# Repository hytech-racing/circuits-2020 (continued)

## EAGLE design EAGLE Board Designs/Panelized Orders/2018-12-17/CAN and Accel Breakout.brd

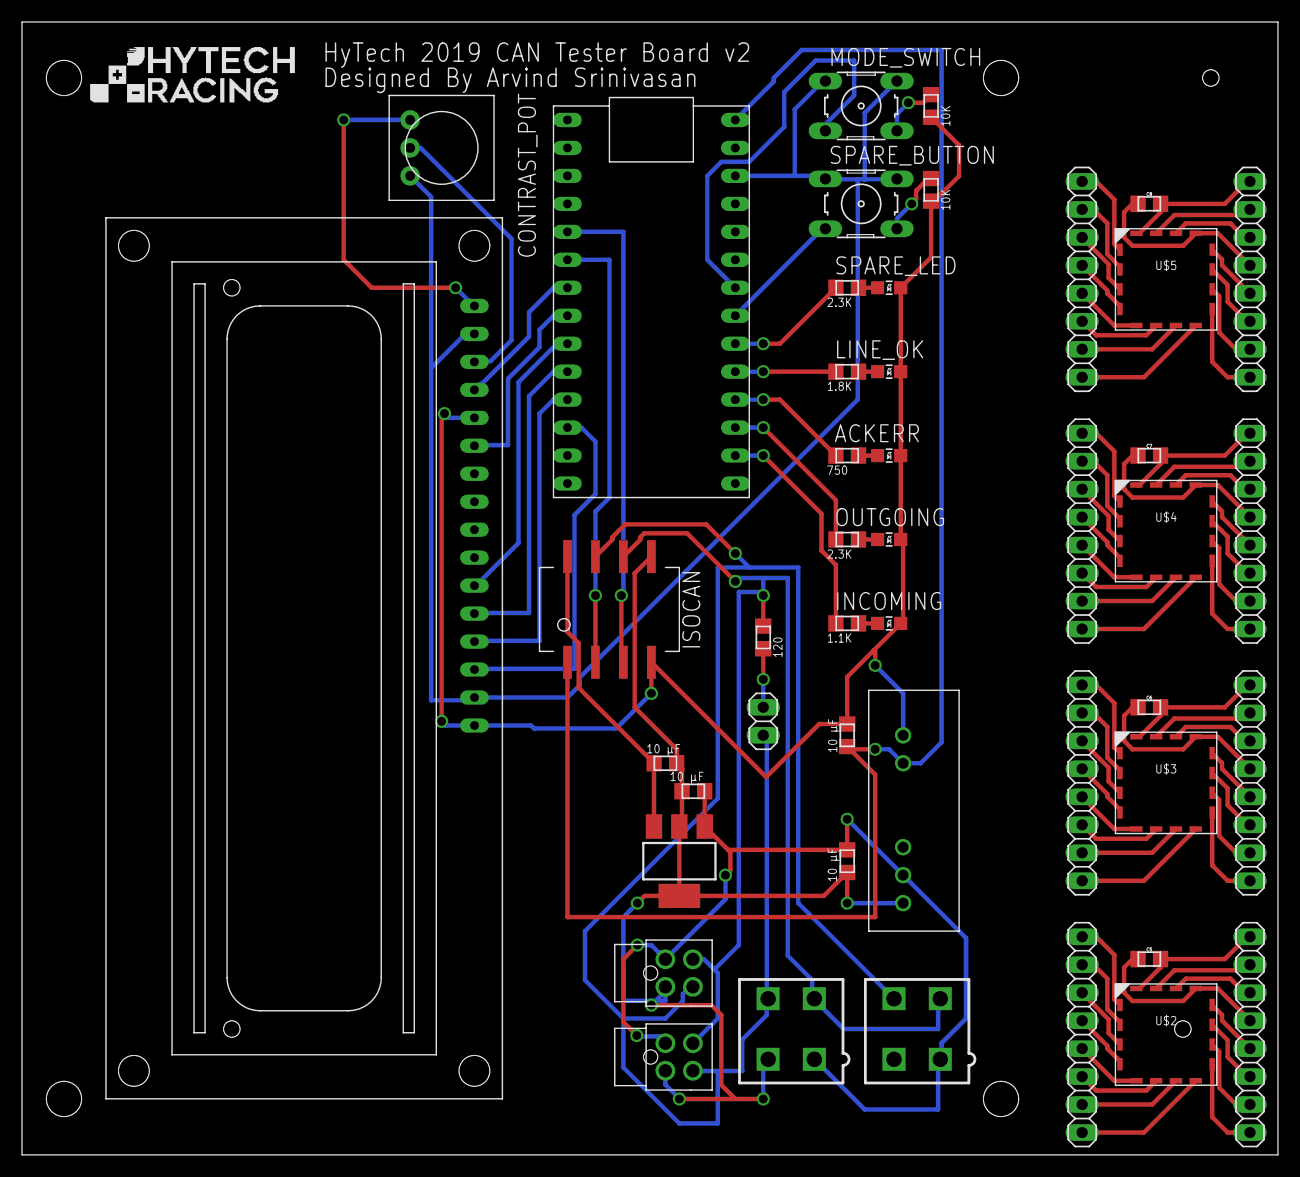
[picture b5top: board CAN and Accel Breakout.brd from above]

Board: 2 copper layers, 114.0 x 102.9 mm, 46 parts (0 on the bottom side), 96 nets.

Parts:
5V_REGULATOR: SOT223
ACKERR: ORANGE; LED-805
C1, C2, C3, C4: 10 μF; 0805
C5, C6, C7, C8: 1µF; 0805
CAN_TERMINATION_RESISTOR: 120; 0805
CONTRAST_POT: 10k; TRIM-3386
INCOMING: YELLOW; LED-805
JP1: M02; 1X02
JP2, JP3, JP4, JP5, JP6, JP7, JP8, JP9: 1X08
LINE_OK: GREEN; LED-805
M1: Minifit-1; MINIFIT_5566-4
M2: Minifit-2; MINIFIT_5566-4
M3: Nanofit-1; NANO-FIT_VERTICAL-4
M4: Nanofit-2; NANO-FIT_VERTICAL-4
MODE_SWITCH: B3F-10XX
OUTGOING: BLUE; LED-805
R1: 1.1K; 0805
R2, R5: 2.3K; 0805
R3: 750; 0805
R4: 1.8K; 0805
R_MODE_SWITCH: 10K; 0805
R_SPARE_BUTTON: 10K; 0805
SPARE_BUTTON: B3F-10XX
SPARE_LED: WHITE; LED-805
U1: ISOCAN; DUB8
U3: TEENSY_3.2_SIMPLE
U4: CHARACTER_LCD; LCD1602
U$1: NCS1S1205SC-12V-5VCONVERTER; DCDC-CONVERTER
U$2, U$3, U$4, U$5: ADIS16209; CC-16-2

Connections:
+3V3_ISOLATED: CONTRAST_POT.3, MODE_SWITCH.1, MODE_SWITCH.2, SPARE_BUTTON.1, SPARE_BUTTON.2, U3.3.3V, U4.2, U4.15
+5V: 5V_REGULATOR.3, C2.1, U1.P$8
+5V_ISOLATED: C3.1, U1.P$1, U3.VIN, U$1.+VOUT
+12V: 5V_REGULATOR.1, C1.1, C4.1, M1.1, M2.1, M3.P$1, M4.P$1, U$1.+VIN
CANH: JP1.1, M1.4, M2.4, M3.P$4, M4.P$4, U1.P$7
CANL: CAN_TERMINATION_RESISTOR.1, M1.3, M2.3, M3.P$3, M4.P$3, U1.P$6
CANRX: U1.P$2, U3.D4(CANRX)
CANTX: U1.P$3, U3.D3(CANTX)
GND: 5V_REGULATOR.2, 5V_REGULATOR.4, C1.2, C2.2, C4.2, M1.2, M2.2, M3.P$2, M4.P$2, U1.P$5, U$1.-VIN
GND1: C5.2, JP3.1, U$2.P$16
GND2: C6.2, JP5.1, U$3.P$16
GND3: C7.2, JP7.1, U$4.P$16
GND4: C8.2, JP9.1, U$5.P$16
GND_ISOLATED: ACKERR.C, C3.2, CONTRAST_POT.1, INCOMING.C, LINE_OK.C, OUTGOING.C, R_MODE_SWITCH.2, R_SPARE_BUTTON.2, SPARE_LED.C, U1.P$4, U3.GND, U4.1, U4.5, U4.16, U$1.-VOUT
unnamed: R1.2, U3.A0
unnamed: R5.1, SPARE_LED.A
unnamed: SPARE_BUTTON.3, U3.A5
unnamed: R2.2, U3.A1
unnamed: R3.2, U3.A2
unnamed: R4.2, U3.A3
unnamed: R5.2, U3.A4
unnamed: LINE_OK.A, R4.1
unnamed: ACKERR.A, R3.1
unnamed: OUTGOING.A, R2.1
unnamed: INCOMING.A, R1.1
unnamed: MODE_SWITCH.4, R_MODE_SWITCH.1
unnamed: MODE_SWITCH.3, U3.A6
unnamed: R_SPARE_BUTTON.1, SPARE_BUTTON.4
unnamed: CAN_TERMINATION_RESISTOR.2, JP1.2
unnamed: JP2.1, U$2.P$1
unnamed: U3.D5, U4.4
unnamed: U3.D6, U4.6
unnamed: U3.D7(RX3), U4.11
unnamed: U3.D8(TX3), U4.12
unnamed: U3.D9(RX2), U4.13
unnamed: U3.D10(TX2), U4.14
unnamed: JP2.2, U$2.P$2
unnamed: JP2.3, U$2.P$3
unnamed: JP2.4, U$2.P$4
unnamed: JP2.5, U$2.P$5
unnamed: JP2.6, U$2.P$6
unnamed: JP2.7, U$2.P$7
unnamed: JP2.8, U$2.P$8
unnamed: JP3.2, U$2.P$15
unnamed: JP3.3, U$2.P$14
unnamed: C5.1, JP3.4, U$2.P$13
unnamed: JP3.5, U$2.P$12
unnamed: JP3.6, U$2.P$11
unnamed: JP3.7, U$2.P$10
unnamed: JP3.8, U$2.P$9
unnamed: JP4.1, U$3.P$1
unnamed: JP4.2, U$3.P$2
unnamed: JP4.3, U$3.P$3
unnamed: JP4.4, U$3.P$4
unnamed: JP4.5, U$3.P$5
unnamed: JP4.6, U$3.P$6
unnamed: JP4.7, U$3.P$7
unnamed: JP4.8, U$3.P$8
unnamed: JP5.2, U$3.P$15
unnamed: JP5.3, U$3.P$14
unnamed: C6.1, JP5.4, U$3.P$13
unnamed: JP5.5, U$3.P$12
unnamed: JP5.6, U$3.P$11
unnamed: JP5.7, U$3.P$10
unnamed: JP5.8, U$3.P$9
unnamed: JP6.1, U$4.P$1
unnamed: JP6.2, U$4.P$2
unnamed: JP6.3, U$4.P$3
unnamed: JP6.4, U$4.P$4
unnamed: JP6.5, U$4.P$5
unnamed: JP6.6, U$4.P$6
unnamed: JP6.7, U$4.P$7
unnamed: JP6.8, U$4.P$8
unnamed: JP7.2, U$4.P$15
unnamed: JP7.3, U$4.P$14
unnamed: C7.1, JP7.4, U$4.P$13
unnamed: JP7.5, U$4.P$12
unnamed: JP7.6, U$4.P$11
unnamed: JP7.7, U$4.P$10
unnamed: JP7.8, U$4.P$9
unnamed: JP8.1, U$5.P$1
unnamed: JP8.2, U$5.P$2
unnamed: JP8.3, U$5.P$3
unnamed: JP8.4, U$5.P$4
unnamed: JP8.5, U$5.P$5
unnamed: JP8.6, U$5.P$6
unnamed: JP8.7, U$5.P$7
unnamed: JP8.8, U$5.P$8
unnamed: JP9.2, U$5.P$15
unnamed: JP9.3, U$5.P$14
unnamed: C8.1, JP9.4, U$5.P$13
unnamed: JP9.5, U$5.P$12
unnamed: JP9.6, U$5.P$11
unnamed: JP9.7, U$5.P$10
unnamed: JP9.8, U$5.P$9
VO: CONTRAST_POT.2, U4.3

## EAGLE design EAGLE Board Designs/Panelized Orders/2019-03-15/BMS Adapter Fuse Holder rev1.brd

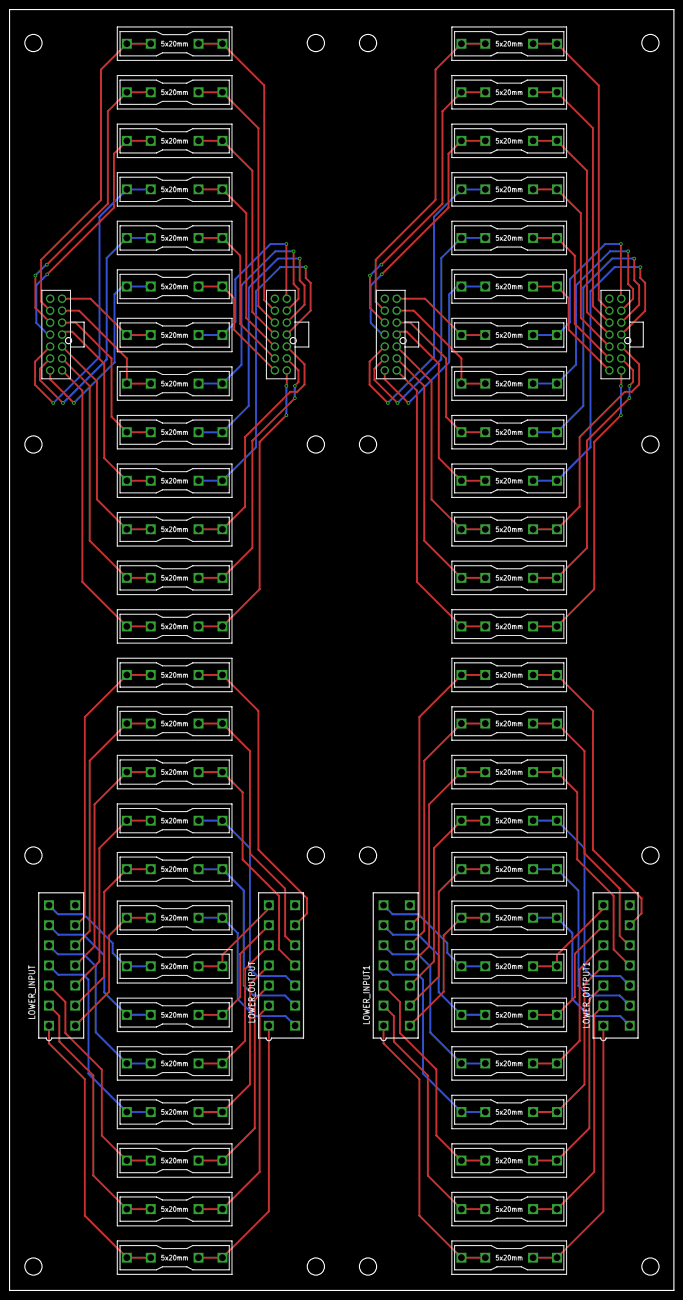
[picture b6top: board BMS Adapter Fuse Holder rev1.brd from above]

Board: 2 copper layers, 139.0 x 268.0 mm, 60 parts (0 on the bottom side), 104 nets.

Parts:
LOWER_INPUT, LOWER_INPUT1: CONNECTOR-14; MINIFIT_5566-14
LOWER_OUTPUT, LOWER_OUTPUT1: CONNECTOR-14; MINIFIT_5566-14
U$1, U$2, U$3, U$4, U$5, U$6, U$7, U$8, U$9, U$10, U$11, U$12, U$13, U$14, U$15, U$16, U$17, U$18, U$19, U$20, U$21, U$22, U$23, U$24, U$25, U$26, U$27, U$28, U$29, U$30, U$31, U$32, U$33, U$34, U$35, U$36, U$37, U$38, U$39, U$40, U$41, U$42, U$43, U$44, U$45, U$46, U$47, U$48, U$49, U$50, U$51, U$52: 1A; 0751.0110
UPPER_INPUT, UPPER_INPUT1: CONNECTOR-14NANO-FIT_VERTICAL-14; NANO-FIT_VERTICAL-14
UPPER_OUTPUT, UPPER_OUTPUT1: CONNECTOR-14NANO-FIT_VERTICAL-14; NANO-FIT_VERTICAL-14

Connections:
unnamed: LOWER_OUTPUT.1, U$1.L1, U$1.L2
unnamed: LOWER_OUTPUT.2, U$2.L1, U$2.L2
unnamed: LOWER_OUTPUT.3, U$3.L1, U$3.L2
unnamed: LOWER_OUTPUT.4, U$4.L1, U$4.L2
unnamed: LOWER_OUTPUT.5, U$5.L1, U$5.L2
unnamed: LOWER_OUTPUT.6, U$6.L1, U$6.L2
unnamed: LOWER_OUTPUT.7, U$7.L1, U$7.L2
unnamed: LOWER_OUTPUT.8, U$8.L1, U$8.L2
unnamed: LOWER_OUTPUT.9, U$9.L1, U$9.L2
unnamed: LOWER_OUTPUT.10, U$10.L1, U$10.L2
unnamed: LOWER_OUTPUT.11, U$11.L1, U$11.L2
unnamed: LOWER_OUTPUT.12, U$12.L1, U$12.L2
unnamed: LOWER_OUTPUT.13, U$13.L1, U$13.L2
unnamed: U$14.L1, U$14.L2, UPPER_OUTPUT.P$1
unnamed: U$15.L1, U$15.L2, UPPER_OUTPUT.P$2
unnamed: U$16.L1, U$16.L2, UPPER_OUTPUT.P$3
unnamed: U$17.L1, U$17.L2, UPPER_OUTPUT.P$4
unnamed: U$18.L1, U$18.L2, UPPER_OUTPUT.P$5
unnamed: U$19.L1, U$19.L2, UPPER_OUTPUT.P$6
unnamed: U$20.L1, U$20.L2, UPPER_OUTPUT.P$7
unnamed: U$21.L1, U$21.L2, UPPER_OUTPUT.P$8
unnamed: U$22.L1, U$22.L2, UPPER_OUTPUT.P$9
unnamed: U$23.L1, U$23.L2, UPPER_OUTPUT.P$10
unnamed: U$24.L1, U$24.L2, UPPER_OUTPUT.P$11
unnamed: U$25.L1, U$25.L2, UPPER_OUTPUT.P$12
unnamed: U$26.L1, U$26.L2, UPPER_OUTPUT.P$13
unnamed: LOWER_OUTPUT1.1, U$27.L1, U$27.L2
unnamed: LOWER_INPUT.1, U$1.R1, U$1.R2
unnamed: LOWER_INPUT.2, U$2.R1, U$2.R2
unnamed: LOWER_INPUT.3, U$3.R1, U$3.R2
unnamed: LOWER_INPUT.4, U$4.R1, U$4.R2
unnamed: LOWER_INPUT.5, U$5.R1, U$5.R2
unnamed: LOWER_INPUT.6, U$6.R1, U$6.R2
unnamed: LOWER_INPUT.7, U$7.R1, U$7.R2
unnamed: LOWER_INPUT.8, U$8.R1, U$8.R2
unnamed: LOWER_INPUT.9, U$9.R1, U$9.R2
unnamed: LOWER_INPUT.10, U$10.R1, U$10.R2
unnamed: LOWER_INPUT.11, U$11.R1, U$11.R2
unnamed: LOWER_INPUT.12, U$12.R1, U$12.R2
unnamed: LOWER_INPUT.13, U$13.R1, U$13.R2
unnamed: U$14.R1, U$14.R2, UPPER_INPUT.P$1
unnamed: U$15.R1, U$15.R2, UPPER_INPUT.P$2
unnamed: U$16.R1, U$16.R2, UPPER_INPUT.P$3
unnamed: U$17.R1, U$17.R2, UPPER_INPUT.P$4
unnamed: U$18.R1, U$18.R2, UPPER_INPUT.P$5
unnamed: U$19.R1, U$19.R2, UPPER_INPUT.P$6
unnamed: U$20.R1, U$20.R2, UPPER_INPUT.P$7
unnamed: U$21.R1, U$21.R2, UPPER_INPUT.P$8
unnamed: U$22.R1, U$22.R2, UPPER_INPUT.P$9
unnamed: U$23.R1, U$23.R2, UPPER_INPUT.P$10
unnamed: U$24.R1, U$24.R2, UPPER_INPUT.P$11
unnamed: U$25.R1, U$25.R2, UPPER_INPUT.P$12
unnamed: U$26.R1, U$26.R2, UPPER_INPUT.P$13
unnamed: LOWER_OUTPUT1.2, U$28.L1, U$28.L2
unnamed: LOWER_OUTPUT1.3, U$29.L1, U$29.L2
unnamed: LOWER_OUTPUT1.4, U$30.L1, U$30.L2
unnamed: LOWER_OUTPUT1.5, U$31.L1, U$31.L2
unnamed: LOWER_OUTPUT1.6, U$32.L1, U$32.L2
unnamed: LOWER_OUTPUT1.7, U$33.L1, U$33.L2
unnamed: LOWER_OUTPUT1.8, U$34.L1, U$34.L2
unnamed: LOWER_OUTPUT1.9, U$35.L1, U$35.L2
unnamed: LOWER_OUTPUT1.10, U$36.L1, U$36.L2
unnamed: LOWER_OUTPUT1.11, U$37.L1, U$37.L2
unnamed: LOWER_OUTPUT1.12, U$38.L1, U$38.L2
unnamed: LOWER_OUTPUT1.13, U$39.L1, U$39.L2
unnamed: U$40.L1, U$40.L2, UPPER_OUTPUT1.P$1
unnamed: U$41.L1, U$41.L2, UPPER_OUTPUT1.P$2
unnamed: U$42.L1, U$42.L2, UPPER_OUTPUT1.P$3
unnamed: U$43.L1, U$43.L2, UPPER_OUTPUT1.P$4
unnamed: U$44.L1, U$44.L2, UPPER_OUTPUT1.P$5
unnamed: U$45.L1, U$45.L2, UPPER_OUTPUT1.P$6
unnamed: U$46.L1, U$46.L2, UPPER_OUTPUT1.P$7
unnamed: U$47.L1, U$47.L2, UPPER_OUTPUT1.P$8
unnamed: U$48.L1, U$48.L2, UPPER_OUTPUT1.P$9
unnamed: U$49.L1, U$49.L2, UPPER_OUTPUT1.P$10
unnamed: U$50.L1, U$50.L2, UPPER_OUTPUT1.P$11
unnamed: U$51.L1, U$51.L2, UPPER_OUTPUT1.P$12
unnamed: U$52.L1, U$52.L2, UPPER_OUTPUT1.P$13
unnamed: LOWER_INPUT1.1, U$27.R1, U$27.R2
unnamed: LOWER_INPUT1.2, U$28.R1, U$28.R2
unnamed: LOWER_INPUT1.3, U$29.R1, U$29.R2
unnamed: LOWER_INPUT1.4, U$30.R1, U$30.R2
unnamed: LOWER_INPUT1.5, U$31.R1, U$31.R2
unnamed: LOWER_INPUT1.6, U$32.R1, U$32.R2
unnamed: LOWER_INPUT1.7, U$33.R1, U$33.R2
unnamed: LOWER_INPUT1.8, U$34.R1, U$34.R2
unnamed: LOWER_INPUT1.9, U$35.R1, U$35.R2
unnamed: LOWER_INPUT1.10, U$36.R1, U$36.R2
unnamed: LOWER_INPUT1.11, U$37.R1, U$37.R2
unnamed: LOWER_INPUT1.12, U$38.R1, U$38.R2
unnamed: LOWER_INPUT1.13, U$39.R1, U$39.R2
unnamed: U$40.R1, U$40.R2, UPPER_INPUT1.P$1
unnamed: U$41.R1, U$41.R2, UPPER_INPUT1.P$2
unnamed: U$42.R1, U$42.R2, UPPER_INPUT1.P$3
unnamed: U$43.R1, U$43.R2, UPPER_INPUT1.P$4
unnamed: U$44.R1, U$44.R2, UPPER_INPUT1.P$5
unnamed: U$45.R1, U$45.R2, UPPER_INPUT1.P$6
unnamed: U$46.R1, U$46.R2, UPPER_INPUT1.P$7
unnamed: U$47.R1, U$47.R2, UPPER_INPUT1.P$8
unnamed: U$48.R1, U$48.R2, UPPER_INPUT1.P$9
unnamed: U$49.R1, U$49.R2, UPPER_INPUT1.P$10
unnamed: U$50.R1, U$50.R2, UPPER_INPUT1.P$11
unnamed: U$51.R1, U$51.R2, UPPER_INPUT1.P$12
unnamed: U$52.R1, U$52.R2, UPPER_INPUT1.P$13
